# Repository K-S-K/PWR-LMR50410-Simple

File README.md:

# PWR-LMR50410-Simple

Simple LMR50410 DC-DC Converter

Fig. 1 Schematics of the Converter

Fig 2. Front view of the PCB

## External documents

[Design rules for JLCPCB](https://forum.kicad.info/t/design-rules-for-jlcpcb/46087)

[Mastering PCB Design Rules: A Comprehensive Guide for Optimal Results](https://jlcpcb.com/blog/a-comprehensive-guide-for-optimal-results)

[PCB Manufacturing & Assembly Capabilities](https://jlcpcb.com/capabilities/pcb-capabilities)

[Simulation examples for KiCad8/KiCad9/Eeschema/ngspice](https://forum.kicad.info/t/simulation-examples-for-kicad8-kicad9-eeschema-ngspice/45546)

## How to uninstall KiCad from macOS

If you install KiCad ‘conventionally’, it gets installed to the following folders.

1. The KiCad folder in "**/Applications**". This contains the main applications.

2. The “kicad” folder is in "**/Library/Application Support**", which contains the assets (footprints/libraries/models/templates), etc.

3. The KiCad preferences in "**~/Library/Preferences/kicad**". Most importantly, these include fp-lib-table and sym-lib-table, as well as various preference files. For 5.99, the preferences are stored separately within a ‘5.99’ directory. You need to remove all the files in this directory to remove all the settings.

This is the standard ‘default’ installation. If you simply remove (3) the next time you run KiCad, it will run the ‘first install’ wizard and regenerate default preferences.

It is, of course, possible to set things up differently and use environmental variables to point to resources in different locations, symlink files to shared locations, and perform multiple other tricks. You can place libraries wherever you like so you need to check the entries in the "**Kicad -> Preferences -> Configure paths ...**" menu to check that there are not any assets that you have relocated that you want to remove.

You will also notice that it is possible to keep a 5.1.x installation and a 5.99 installation separate with different preferences, and you need to remove the 5.99 folder if you want to reset this as well.

When you reinstall KiCad, if there is a pre-existing ‘kicad’ folder in "**~/Library/Preferences**", you KEEP your original preferences. This is the only directory you need to remove to reset to ‘factory fresh’. This is a common paradigm on macOS - if you have futzed up an applications setting and can’t seem to reset it or it doesn’t start, deleting the preferences is a good way of resting the app back to its ‘out of the box’ settings.

---

In addition and for completeness, the "**~/Library/Preferences/kicad/**" folder contains a scripting folder. This is used for plugins, and you might want to preserve the contents between installs to keep any plugins. On a practical point, it is probably easiest for maintenance to symlink the original files into the scripting directory.

There are plans for the forthcoming v6 to have a plugin manager. At present, the scripts are in "**~/Library/Preferences/kicad/5.99/scripting**".

The following directories are also searched for plugins, which are where the stock footprint wizards live.

"**/Applications/KiCad/KiCad.app/Contents/SharedSupport/scripting**"
"**/Applications/KiCad/KiCad.app/Contents/SharedSupport/scripting/plugins**"

(Based on [the KiCad forum message](https://forum.kicad.info/t/mac-os-how-to-remove-it-all/31264/2)).

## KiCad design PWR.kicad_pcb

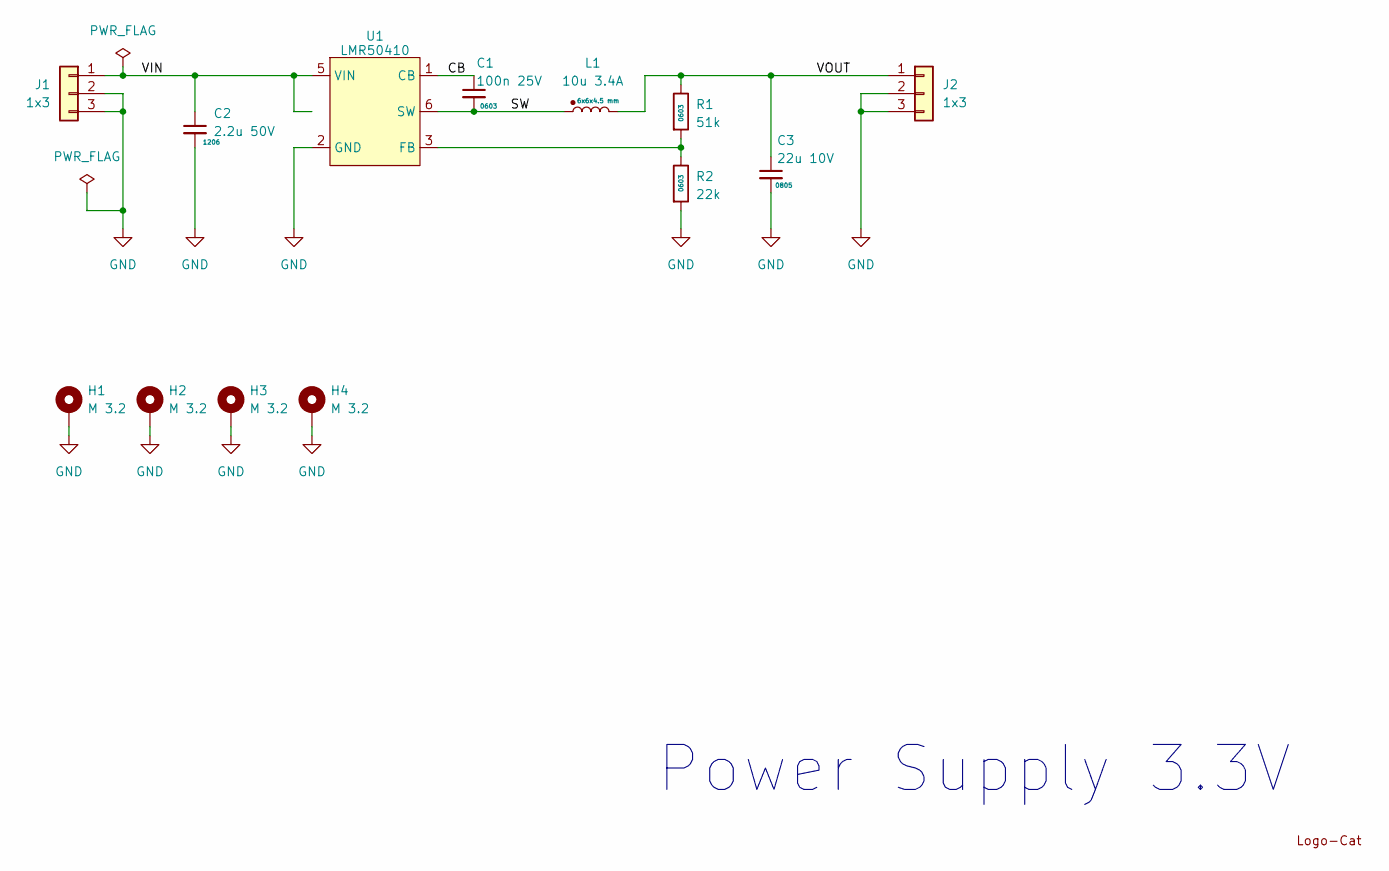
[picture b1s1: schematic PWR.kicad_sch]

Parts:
C1: 100n 25V; C_0603_1608Metric
C2: 2.2u 50V; C_1206_3216Metric
C3: 22u 10V; C_0805_2012Metric
H1, H2, H3, H4: M 3.2; MountingHole_3.2mm_M3_DIN965_Pad
J1, J2: 1x3; PinHeader_1x03_P2.54mm_Vertical
L1: 10u 3.4A; L_VLS6045EX
Logo2: Logo_Cat
R1: 51k; R_0603_1608Metric
R2: 22k; R_0603_1608Metric
U1: LMR50410; SOT-23-6

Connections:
/CB: C1.1, U1.1 (CB)
/SW: C1.2, L1.1, U1.6 (SW)
/VIN: C2.1, J1.1, U1.4 (EN), U1.5 (VIN)
/VOUT: C3.1, J2.1, L1.2, R1.1
GND: C2.2, C3.2, H1.1, H2.1, H3.1, H4.1, J1.2, J1.3, J2.2, J2.3, R2.2, U1.2 (GND)
unnamed: R1.2, R2.1, U1.3 (FB)

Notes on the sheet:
Power Supply 3.3V

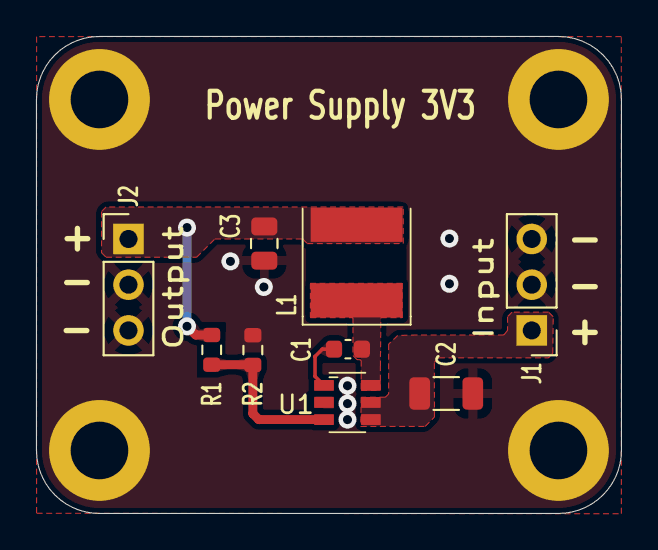
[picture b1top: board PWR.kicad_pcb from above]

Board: 2 copper layers, 32.5 x 26.5 mm, 14 parts (1 on the bottom side), 6 nets.

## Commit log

2025-10-25 Add the Project Content
2025-10-25 Apply JLCPCB Rules
2025-10-25 Add external documents section to README
    Added external documents section with relevant links.
2025-10-25 Add uninstall instructions for KiCad on macOS
    Added instructions for uninstalling KiCad from macOS, detailing folder locations and preferences management.
2026-03-22 Update the documentation
2026-03-22 Remove redundant documentation content
